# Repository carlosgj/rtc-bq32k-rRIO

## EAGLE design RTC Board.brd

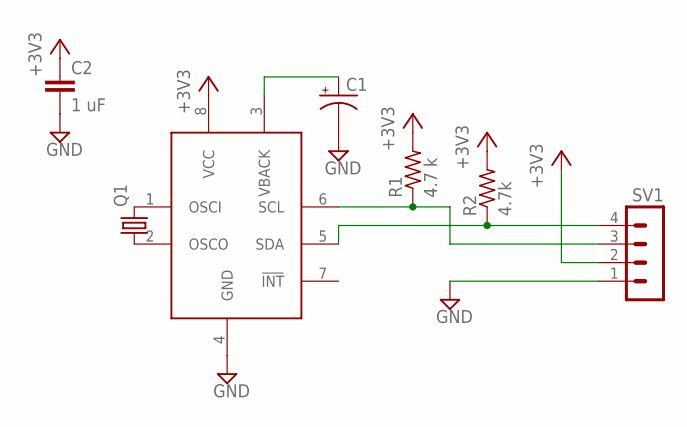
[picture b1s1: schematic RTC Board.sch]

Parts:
C1: CPOL-US150CLZ-1010; 150CLZ-1010
C2: 1 uF; C1206
Q1: CRYSTALTC26H; TC26H
R1: 4.7 k; R1206
R2: 4.7k; R1206
SV1: MA04-1
U$1: BQ32000; SOIC8

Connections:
+3V3: C2.1, R1.2, R2.2, SV1.2, U$1.8 (VCC)
GND: C1.-, C2.2, SV1.1, U$1.4 (GND)
unnamed: C1.+, U$1.3 (VBACK)
unnamed: Q1.2, U$1.1 (OSCI)
unnamed: Q1.1, U$1.2 (OSCO)
unnamed: R1.1, SV1.3, U$1.6 (SCL)
unnamed: R2.1, SV1.4, U$1.5 (SDA)

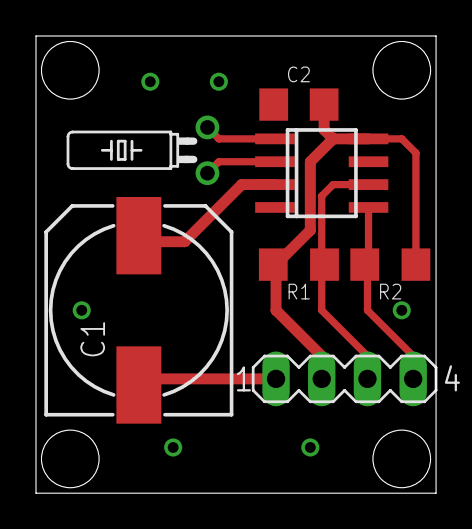
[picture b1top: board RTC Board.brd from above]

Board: 2 copper layers, 22.2 x 25.4 mm, 7 parts (0 on the bottom side), 7 nets.

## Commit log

2019-01-23 Adding EAGLE files for custom BQ32000 board
